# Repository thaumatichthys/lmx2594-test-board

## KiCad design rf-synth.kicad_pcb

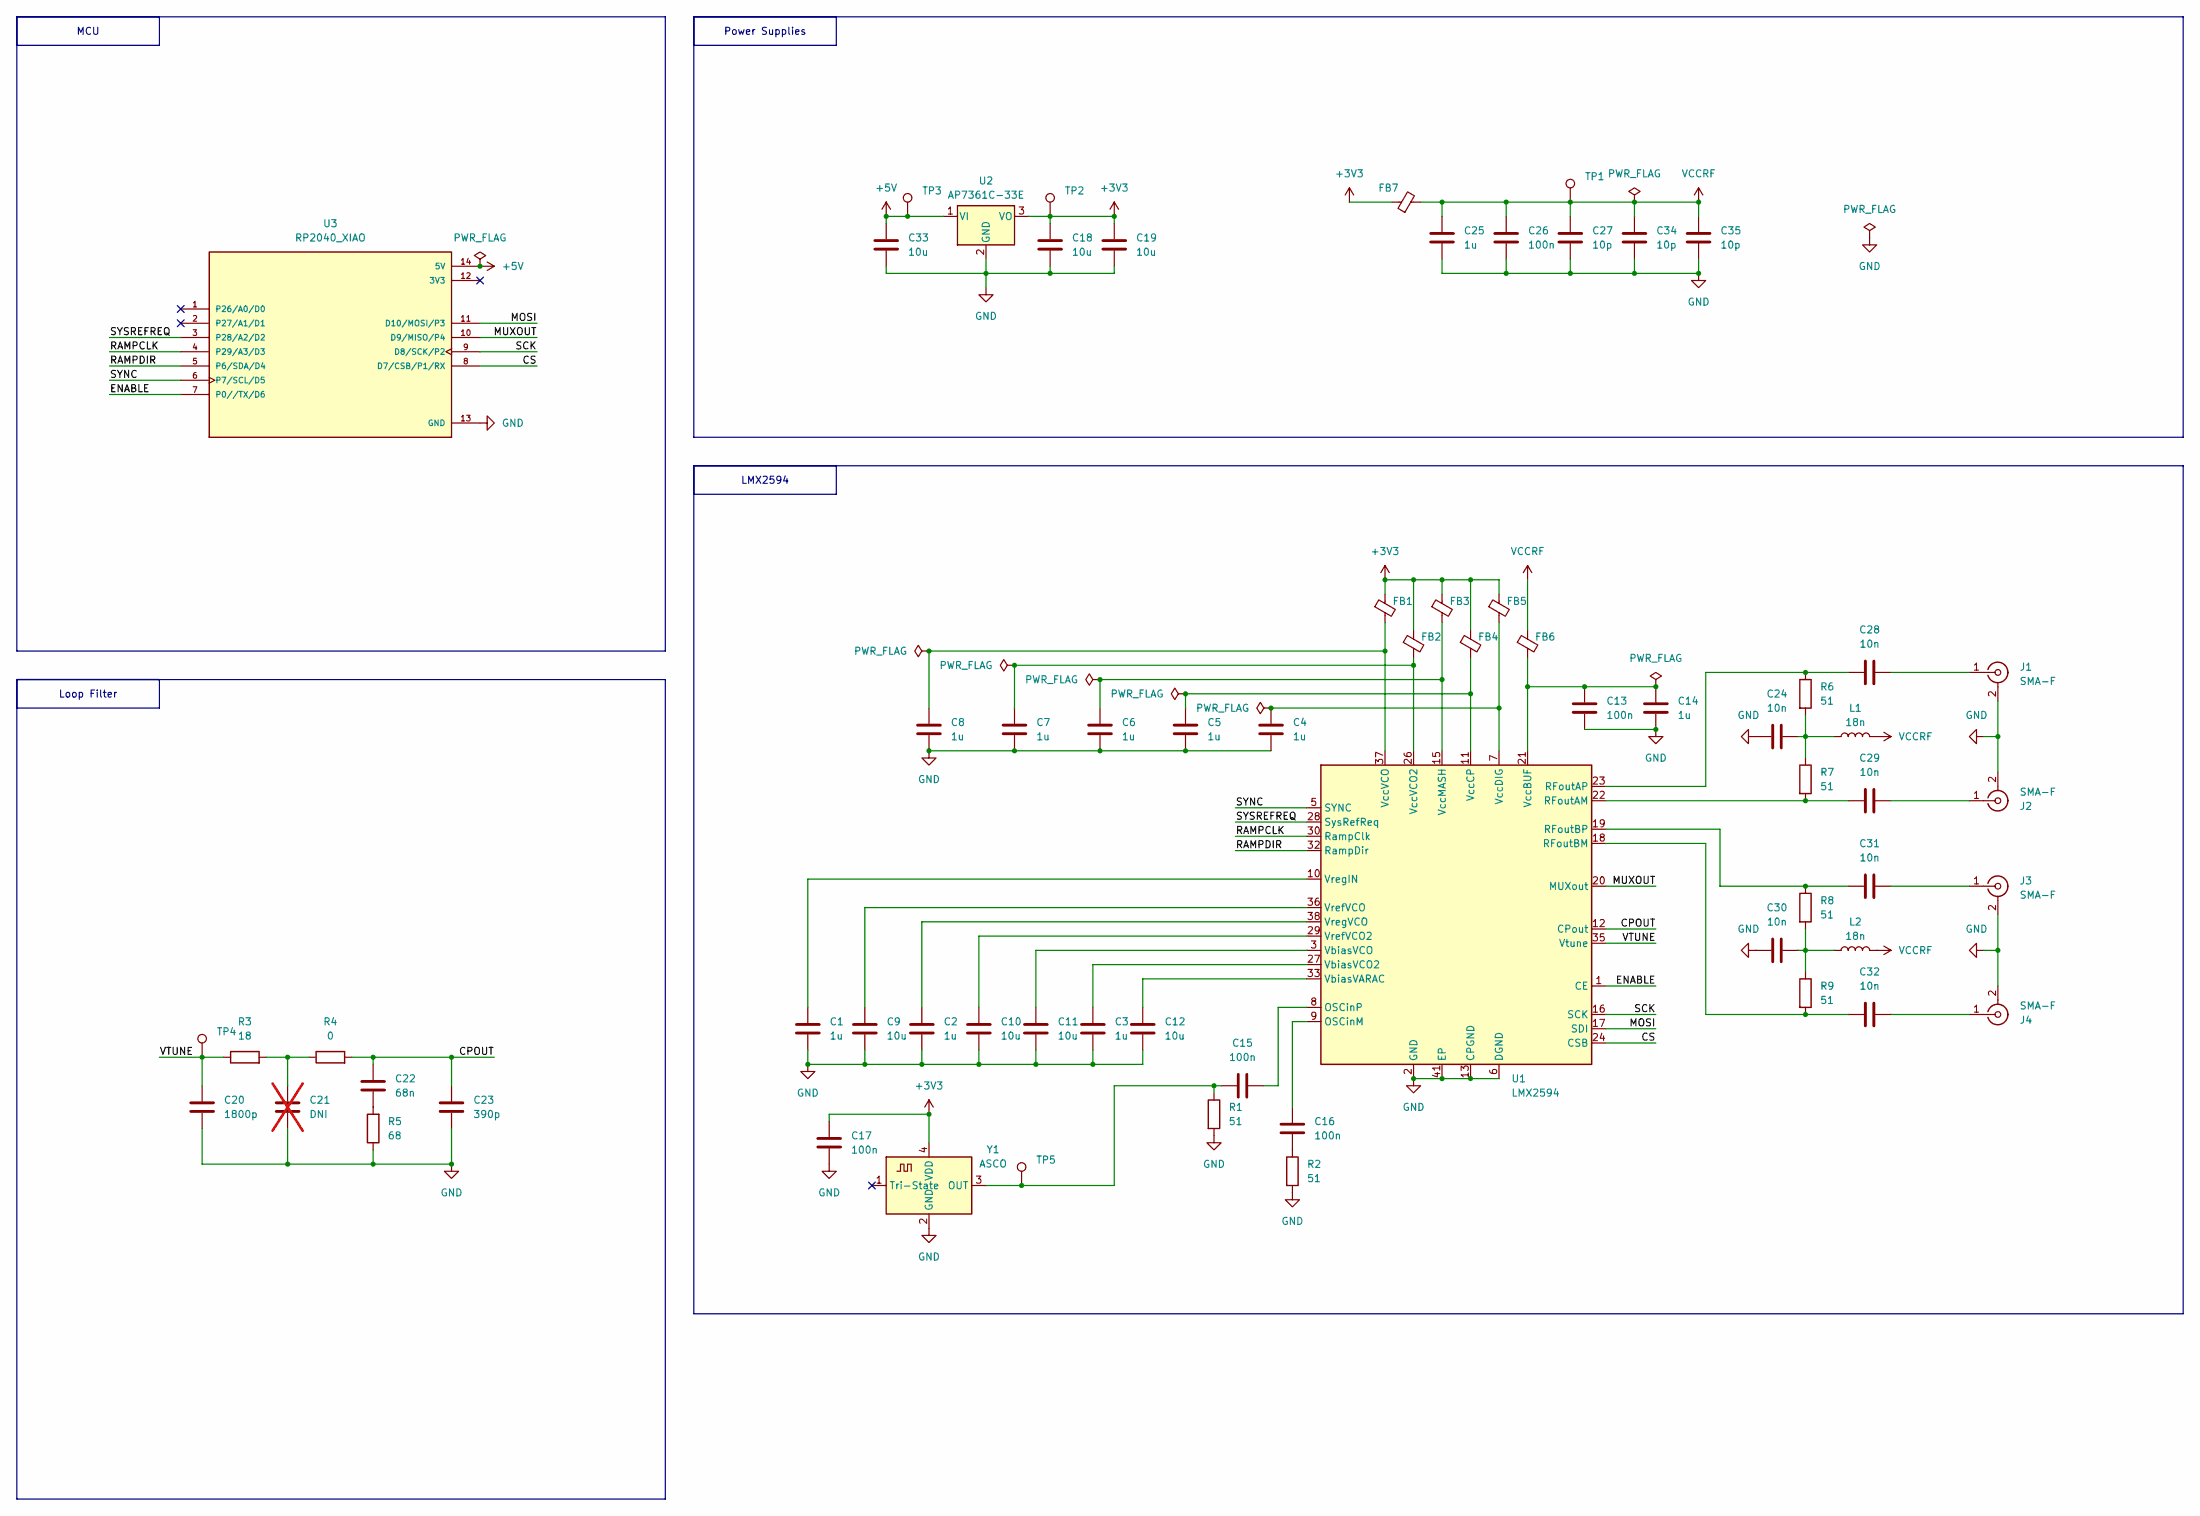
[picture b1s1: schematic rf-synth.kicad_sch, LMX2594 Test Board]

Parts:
C1, C2, C3, C4, C5, C6, C7, C8, C14, C25: 1u; C_0402_1005Metric_Pad0.74x0.62mm_HandSolder
C9, C10, C11, C12, C18, C19, C33: 10u; C_0603_1608Metric_Pad1.08x0.95mm_HandSolder
C13, C15, C16, C17, C26: 100n; C_0402_1005Metric_Pad0.74x0.62mm_HandSolder
C20: 1800p; C_0603_1608Metric_Pad1.08x0.95mm_HandSolder
C21: DNI; C_0603_1608Metric_Pad1.08x0.95mm_HandSolder; not fitted
C22: 68n; C_0603_1608Metric_Pad1.08x0.95mm_HandSolder
C23: 390p; C_0603_1608Metric_Pad1.08x0.95mm_HandSolder
C24, C28, C29, C30, C31, C32: 10n; C_0402_1005Metric_Pad0.74x0.62mm_HandSolder
C27, C34, C35: 10p; C_0402_1005Metric_Pad0.74x0.62mm_HandSolder
FB1, FB2, FB3, FB4, FB5, FB6, FB7: BLM18PG121SN1D; L_0603_1608Metric_Pad1.05x0.95mm_HandSolder
J1, J2, J3, J4: SMA-F; ADAMTECH_RF2-143-T-17-50-G
L1, L2: 18n; L_0402_1005Metric_Pad0.77x0.64mm_HandSolder
R1, R2, R6, R7, R8, R9: 51; R_0402_1005Metric_Pad0.72x0.64mm_HandSolder
R3: 18; R_0603_1608Metric_Pad0.98x0.95mm_HandSolder
R4: 0; R_0603_1608Metric_Pad0.98x0.95mm_HandSolder
R5: 68; R_0603_1608Metric_Pad0.98x0.95mm_HandSolder
TP1, TP2, TP3, TP4, TP5: TestPoint; TestPoint_Pad_1.0x1.0mm
U1: LMX2594; VQFN-40-1EP_6x6mm_P0.5mm_EP3.5x3.5mm
U2: AP7361C-33E; SOT-223-3_TabPin2
U3: RP2040_XIAO; MODULE_102010428; PARTREV 1.3
Y1: ASCO; OSC_TG2016SMN_48.0000M-ECGNNM0

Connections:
+3V3: C17.2, C18.1, C19.1, FB1.1, FB2.1, FB3.1, FB4.1, FB5.1, FB7.1, TP2.1, U2.3 (VO), Y1.4 (VDD)
+5V: C33.1, TP3.1, U2.1 (VI), U3.14 (5V)
/CPOUT: C22.1, C23.1, R4.2, U1.12 (CPout)
/CS: U1.24 (CSB), U3.8 (D7/CSB/P1/RX)
/ENABLE: U1.1 (CE), U3.7 (P0//TX/D6)
/MOSI: U1.17 (SDI), U3.11 (D10/MOSI/P3)
/MUXOUT: U1.20 (MUXout), U3.10 (D9/MISO/P4)
/RAMPCLK: U1.30 (RampClk), U3.4 (P29/A3/D3)
/RAMPDIR: U1.32 (RampDir), U3.5 (P6/SDA/D4)
/SCK: U1.16 (SCK), U3.9 (D8/SCK/P2)
/SYNC: U1.5 (SYNC), U3.6 (P7/SCL/D5)
/SYSREFREQ: U1.28 (SysRefReq), U3.3 (P28/A2/D2)
/VTUNE: C20.1, R3.1, TP4.1, U1.35 (Vtune)
GND: C1.2, C2.2, C3.2, C4.2, C5.2, C6.2, C7.2, C8.2, C9.2, C10.2, C11.2, C12.2, C13.2, C14.2, C17.1, C18.2, C19.2, C20.2, C21.2, C23.2, C24.1, C25.2, C26.2, C27.2, C30.1, C33.2, C34.2, C35.2, J1.2 (Ext), J2.2 (Ext), J3.2 (Ext), J4.2 (Ext), R1.2, R2.2, R5.1, U1.2 (GND), U1.4 (GND), U1.6 (DGND), U1.13 (CPGND), U1.14 (DGND), U1.25 (GND), U1.31 (GND), U1.34 (GND), U1.39 (GND), U1.40 (GND), U1.41 (EP), U2.2 (GND), U3.13 (GND), Y1.2 (GND)
unnamed: C16.1, R2.1
unnamed: C21.1, R3.2, R4.1
unnamed: C22.2, R5.2
unnamed: C24.2, L1.1, R6.2, R7.1
unnamed: C30.2, L2.1, R8.2, R9.1
unnamed: C28.2, J1.1 (In)
unnamed: C29.2, J2.1 (In)
unnamed: C31.2, J3.1 (In)
unnamed: C32.2, J4.1 (In)
unnamed: C16.2, U1.9 (OSCinM)
unnamed: C15.2, U1.8 (OSCinP)
unnamed: C29.1, R7.2, U1.22 (RFoutAM)
unnamed: C28.1, R6.1, U1.23 (RFoutAP)
unnamed: C32.1, R9.2, U1.18 (RFoutBM)
unnamed: C31.1, R8.1, U1.19 (RFoutBP)
unnamed: C12.1, U1.33 (VbiasVARAC)
unnamed: C3.1, U1.27 (VbiasVCO2)
unnamed: C11.1, U1.3 (VbiasVCO)
unnamed: C13.1, C14.1, FB6.2, U1.21 (VccBUF)
unnamed: C5.1, FB4.2, U1.11 (VccCP)
unnamed: C4.1, FB5.2, U1.7 (VccDIG)
unnamed: C6.1, FB3.2, U1.15 (VccMASH)
unnamed: C7.1, FB2.2, U1.26 (VccVCO2)
unnamed: C8.1, FB1.2, U1.37 (VccVCO)
unnamed: C10.1, U1.29 (VrefVCO2)
unnamed: C9.1, U1.36 (VrefVCO)
unnamed: C1.1, U1.10 (VregIN)
unnamed: C2.1, U1.38 (VregVCO)
unnamed: C15.1, R1.1, TP5.1, Y1.3 (OUT)
VCCRF: C25.1, C26.1, C27.1, C34.1, C35.1, FB6.1, FB7.2, L1.2, L2.2, TP1.1

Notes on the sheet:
Power Supplies
LMX2594
MCU
Loop Filter

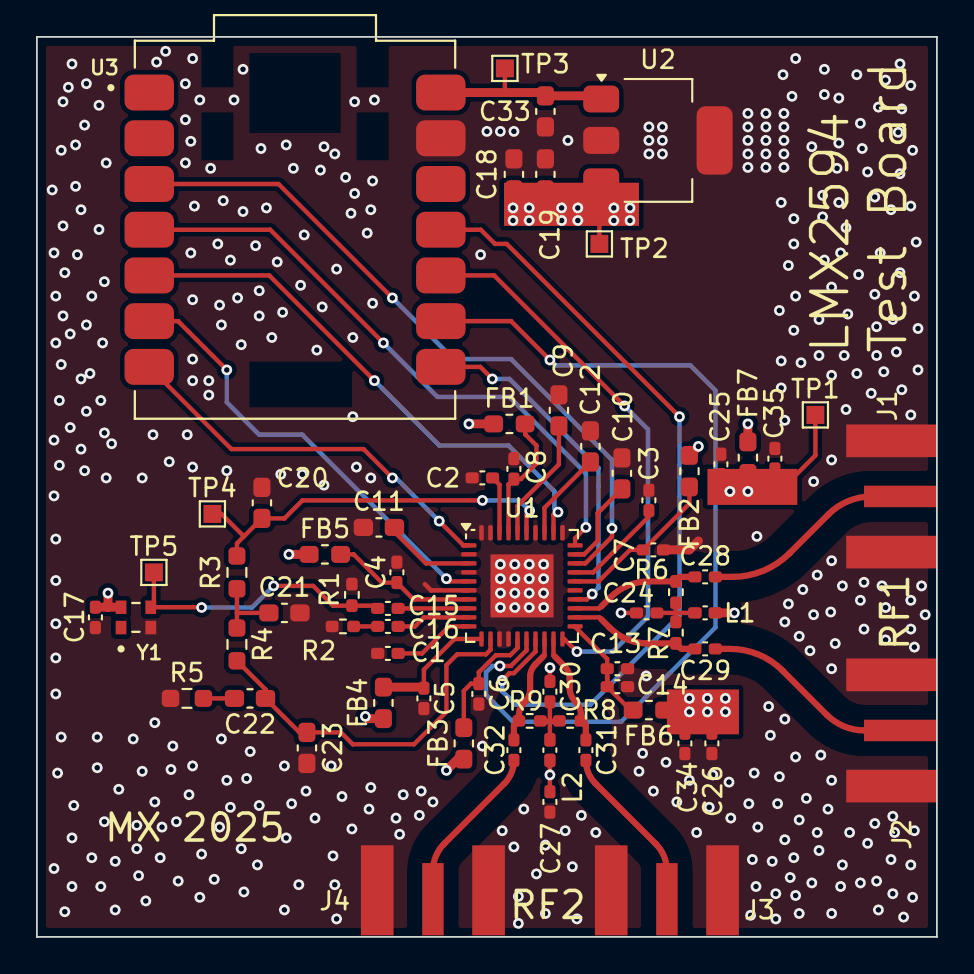
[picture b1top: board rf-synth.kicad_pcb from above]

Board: 4 copper layers, 50.0 x 50.0 mm, 66 parts (0 on the bottom side), 44 nets.

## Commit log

2025-09-25 routed some
2025-09-26 routed more
2025-09-26 maybe fucked
2025-09-26 finished board mostly
